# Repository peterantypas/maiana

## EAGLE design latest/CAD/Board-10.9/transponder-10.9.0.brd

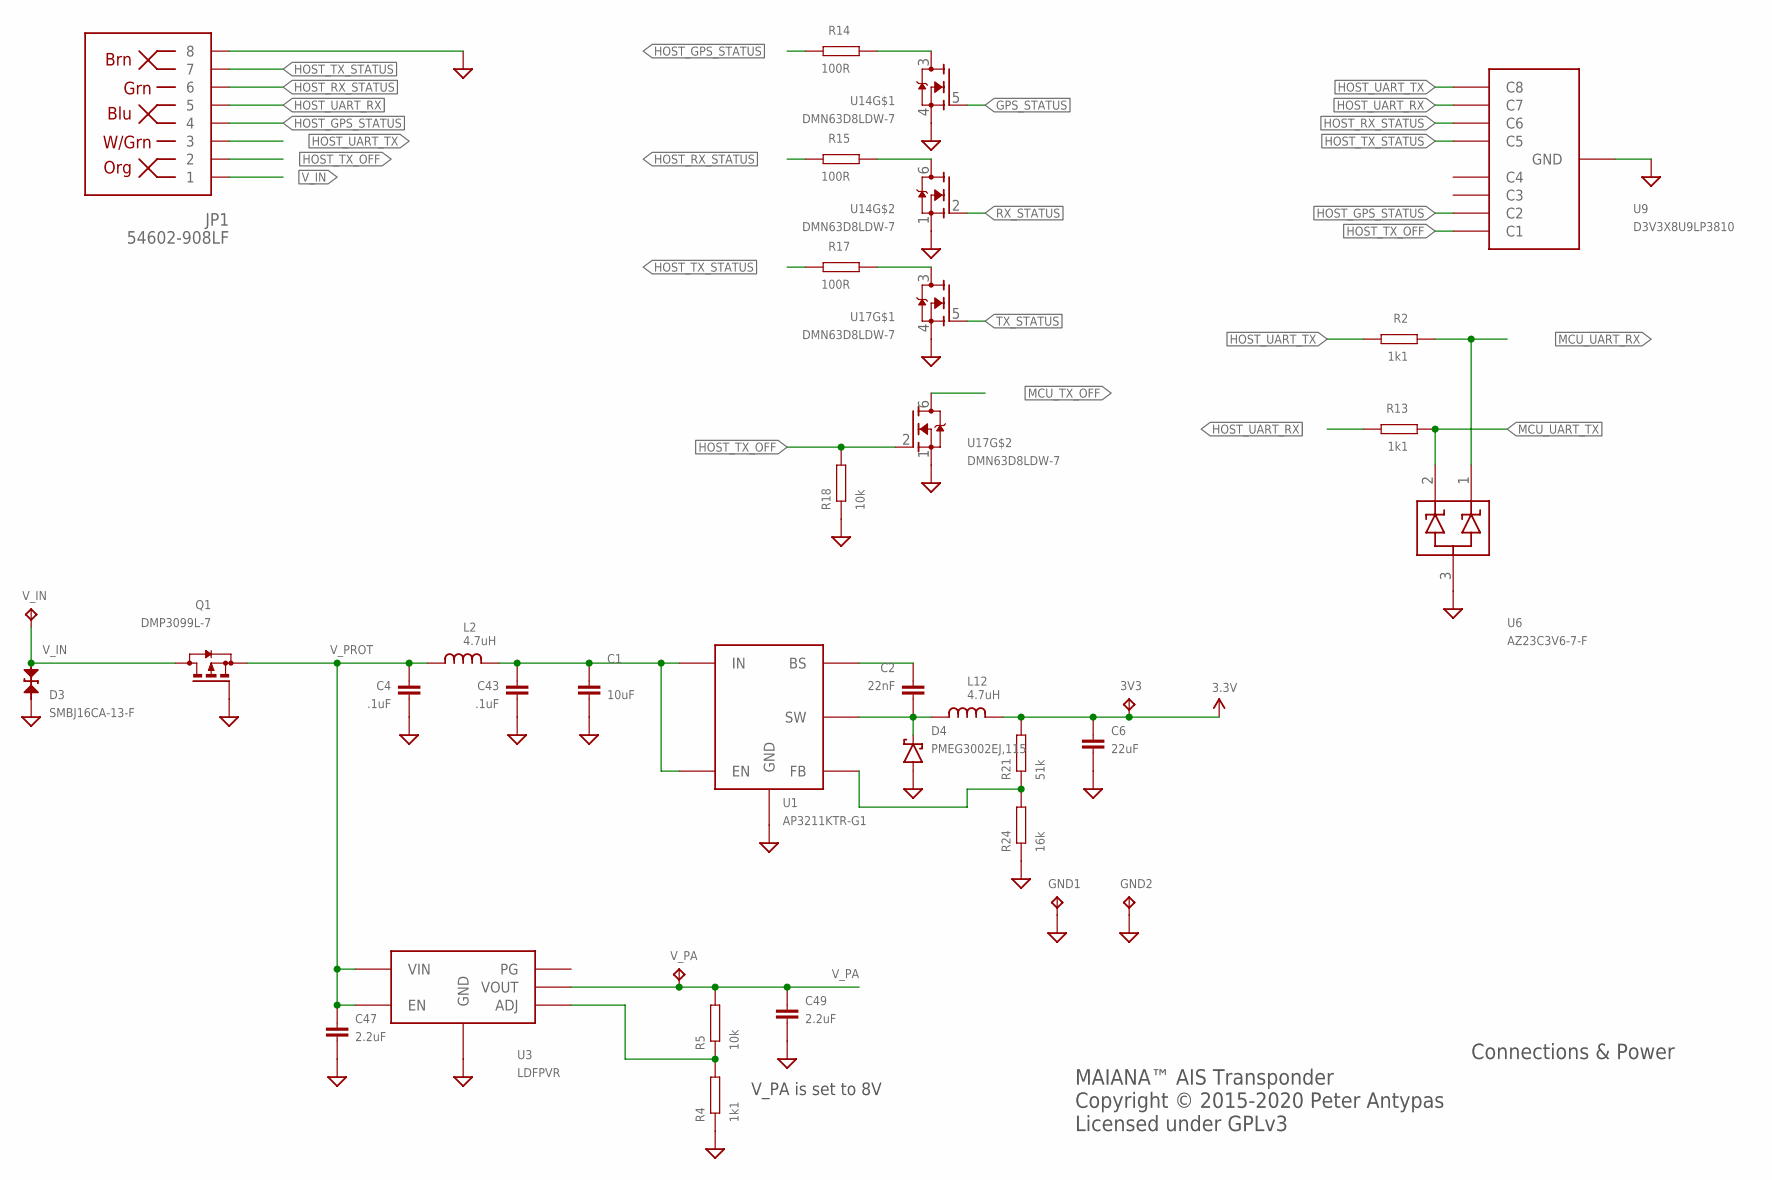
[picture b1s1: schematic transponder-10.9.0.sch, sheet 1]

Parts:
3V3: TPTP12R; TP12R
C1: 10uF; 0805; PARTNO EMK212ABJ106KG-T
C2: 22nF; 0603; PARTNO GRM188R71E223KA01D
C4, C43: .1uF; 0603; PARTNO EMK107B7104KAHT
C6: 22uF; 0805; PARTNO *
C47, C49: 2.2uF; 0603; PARTNO EMK107BJ225KA-T
D3: SMBJ16CA-13-F; SMB-BIDIR; PARTNO SMBJ16CA-13-F
D4: PMEG3002EJ,115; SOD323; PARTNO NSR0240HT1G
GND1, GND2: TPTP12R; TP12R
JP1: 54602-908LF; RJ45-8; PARTNO 54602-908LF‎
L2, L12: 4.7uH; 0805; PARTNO MLZ2012M4R7WT000
Q1: DMP3099L-7; SOT23; PARTNO DMP3099L-7
R2, R4, R13: 1k1; 0603; PARTNO RC0603JR-071K1L
R5, R18: 10k; 0603; PARTNO RC0603JR-0710KL
R14, R15: 100R; 0603; PARTNO RC0603JR-07100RL
R17: 100R; 0603; PARTNO RC0603JR-070RL
R21: 51k; 0603; PARTNO RC0603JR-0751KL
R24: 16k; 0603; PARTNO RC0603FR-1016KL
U1: AP3211KTR-G1; SOT23-6; PARTNO AP3211KTR-G1
U3: LDFPVR; DFN6-2X2; PARTNO LDFPUR
U6: AZ23C3V6-7-F; SOT-23
U9: D3V3X8U9LP3810; U-DFN3810-9(B)
U14, U17: DMN63D8LDW-7; SOT363; PARTNO DMN63D8LDW-7
V_IN: TPTP12R; TP12R
V_PA: TPTP12R; TP12R

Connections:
3.3V: 3V3.TP, C6.P$1 (1), L12.P$2 (2), R21.P$2; also elsewhere on the board
GND: C1.P$2 (2), C4.P$2 (2), C6.P$2 (2), C43.P$2 (2), C47.P$2 (2), C49.P$2 (2), D3.C, D4.A, GND1.TP, GND2.TP, JP1.8, Q1.1 (G), R4.P$1, R18.P$1, R24.P$1, U1.2 (GND), U3.P$4 (GND), U3.P$7 (GND), U6.3, U9.P$3 (GND), U14.1 (S), U14.4 (S), U17.1 (S), U17.4 (S); also elsewhere on the board
GPS_STATUS: U14.5 (G); also elsewhere on the board
HOST_GPS_STATUS: JP1.4, R14.P$2, U9.P$2 (C2)
HOST_RX_STATUS: JP1.6, R15.P$2, U9.P$7 (C6)
HOST_TX_OFF: JP1.2, R18.P$2, U9.P$1 (C1), U17.2 (G)
HOST_TX_STATUS: JP1.7, R17.P$2, U9.P$6 (C5)
HOST_UART_RX: JP1.5, R13.P$2, U9.P$8 (C7)
HOST_UART_TX: JP1.3, R2.P$2, U9.P$9 (C8)
MCU_TX_OFF: U17.6 (D); also elsewhere on the board
MCU_UART_RX: R2.P$1, U6.1; also elsewhere on the board
MCU_UART_TX: R13.P$1, U6.2; also elsewhere on the board
unnamed: C2.P$2 (2), D4.C, L12.P$1 (1), U1.6 (SW)
unnamed: R14.P$1, U14.3 (D)
unnamed: R15.P$1, U14.6 (D)
unnamed: R17.P$1, U17.3 (D)
unnamed: C2.P$1 (1), U1.1 (BS)
unnamed: R21.P$1, R24.P$2, U1.3 (FB)
unnamed: C1.P$1 (1), C43.P$1 (1), L2.P$2 (2), U1.4 (EN), U1.5 (IN)
unnamed: R4.P$2, R5.P$1, U3.P$2 (ADJ)
RX_STATUS: U14.2 (G); also elsewhere on the board
TX_STATUS: U17.5 (G); also elsewhere on the board
V_IN: D3.A, JP1.1, Q1.3 (D), V_IN.TP
V_PA: C49.P$1 (1), R5.P$2, U3.P$1 (VOUT), V_PA.TP; also elsewhere on the board
V_PROT: C4.P$1 (1), C47.P$1 (1), L2.P$1 (1), Q1.2 (S), U3.P$5 (EN), U3.P$6 (VIN)

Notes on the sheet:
Connections & Power
MAIANA™ AIS Transponder Copyright © 2015-2020 Peter Antypas Licensed under GPLv3
V_PA is set to 8V

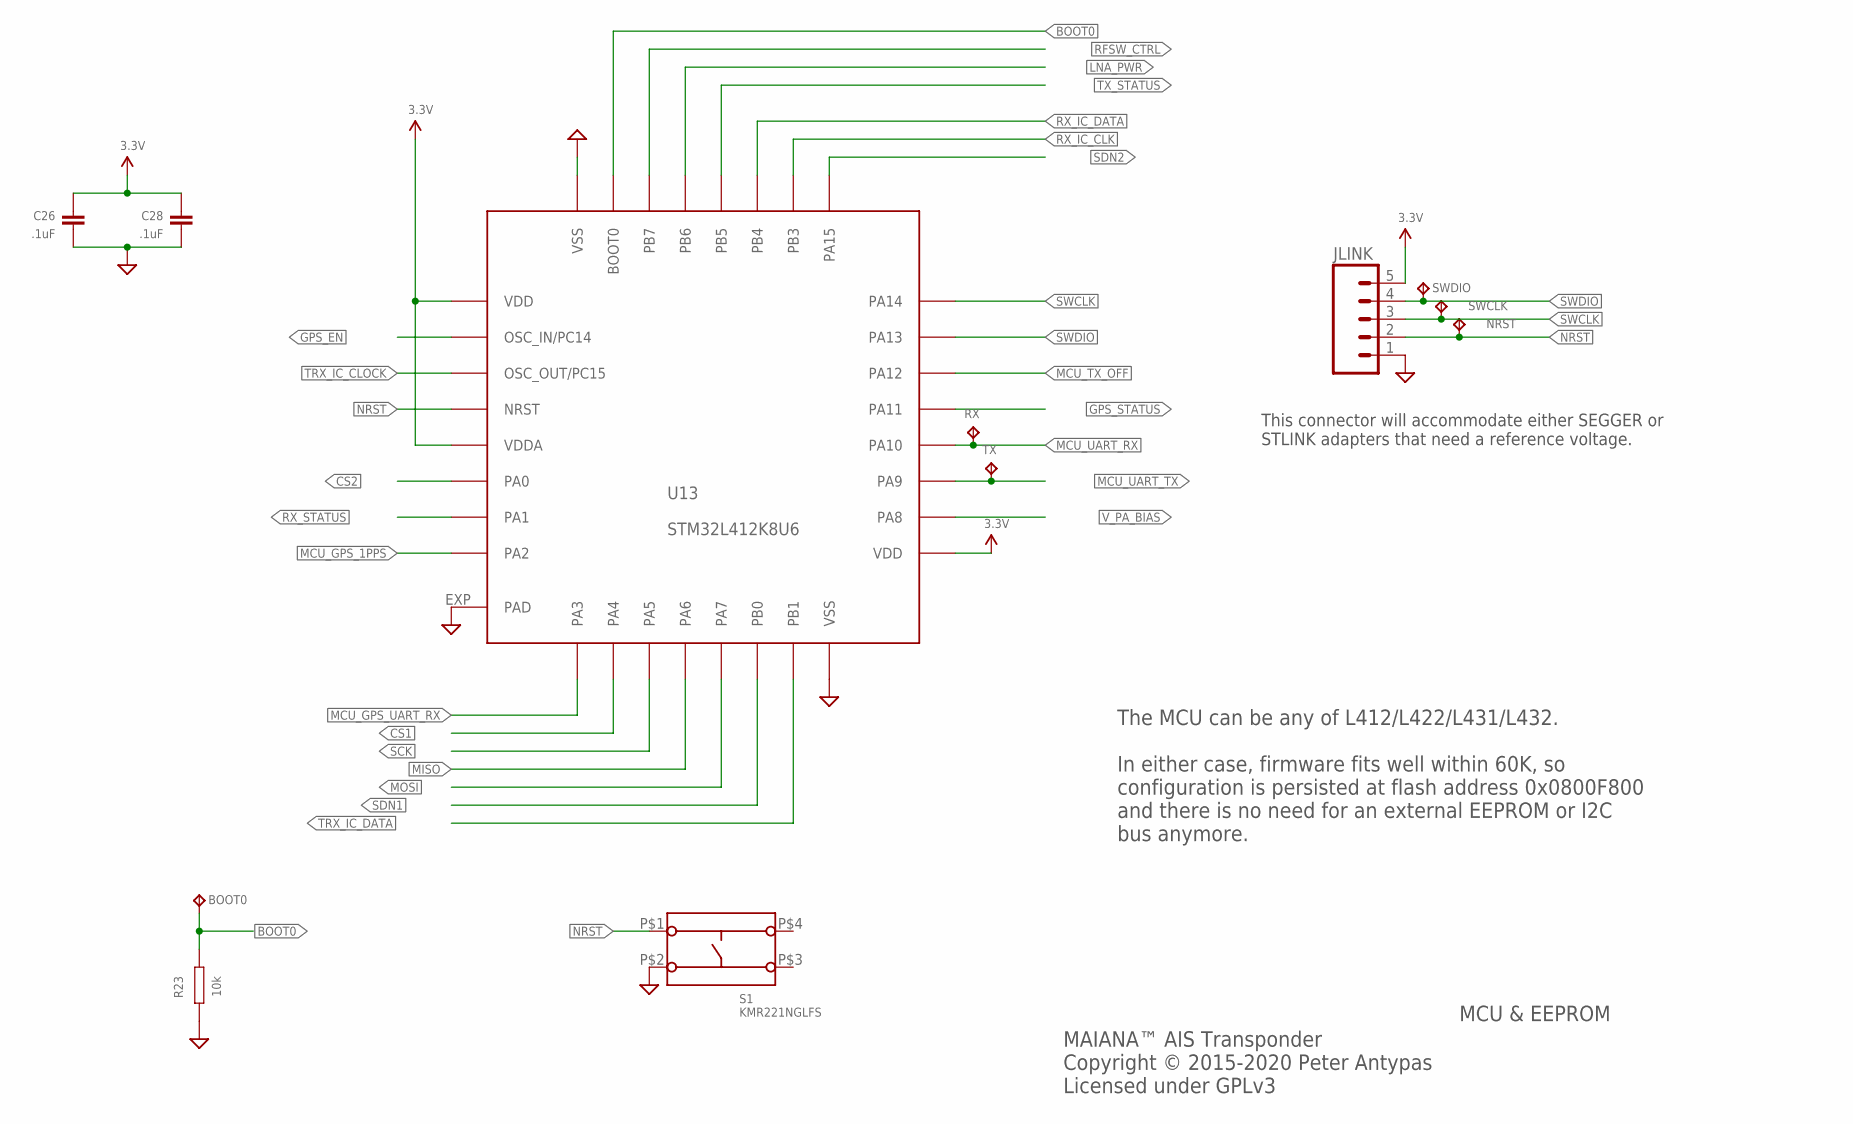
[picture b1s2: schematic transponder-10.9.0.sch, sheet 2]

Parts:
BOOT0: TPTP12R; TP12R
C26, C28: .1uF; 0603; PARTNO EMK107B7104KAHT
JLINK: M05PTH; 1X05
NRST: TPTP12R; TP12R
R23: 10k; 0603; PARTNO RC0603JR-0710KL
RX: TPTP12R; TP12R
S1: KMR221NGLFS
SWCLK: TPTP12R; TP12R
SWDIO: TPTP12R; TP12R
TX: TPTP12R; TP12R
U13: STM32L412K8U6; QFN32; PARTNO STM32L412K8U6

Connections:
3.3V: C26.P$1 (1), C28.P$1 (1), JLINK.5, U13.1 (VDD), U13.5 (VDDA), U13.17 (VDD); also elsewhere on the board
BOOT0: BOOT0.TP, R23.P$1, U13.31 (BOOT0)
CS1: U13.10 (PA4); also elsewhere on the board
CS2: U13.6 (PA0); also elsewhere on the board
GND: C26.P$2 (2), C28.P$2 (2), JLINK.1, R23.P$2, S1.P$2 (S2), U13.16 (VSS), U13.32 (VSS), U13.EXP (PAD); also elsewhere on the board
GPS_EN: U13.2 (OSC_IN/PC14); also elsewhere on the board
GPS_STATUS: U13.21 (PA11); also elsewhere on the board
LNA_PWR: U13.29 (PB6); also elsewhere on the board
MCU_GPS_1PPS: U13.8 (PA2); also elsewhere on the board
MCU_GPS_UART_RX: U13.9 (PA3); also elsewhere on the board
MCU_TX_OFF: U13.22 (PA12); also elsewhere on the board
MCU_UART_RX: RX.TP, U13.20 (PA10); also elsewhere on the board
MCU_UART_TX: TX.TP, U13.19 (PA9); also elsewhere on the board
MISO: U13.12 (PA6); also elsewhere on the board
MOSI: U13.13 (PA7); also elsewhere on the board
NRST: JLINK.2, NRST.TP, S1.P$1 (S1), U13.4 (NRST)
RFSW_CTRL: U13.30 (PB7); also elsewhere on the board
RX_IC_CLK: U13.26 (PB3); also elsewhere on the board
RX_IC_DATA: U13.27 (PB4); also elsewhere on the board
RX_STATUS: U13.7 (PA1); also elsewhere on the board
SCK: U13.11 (PA5); also elsewhere on the board
SDN1: U13.14 (PB0); also elsewhere on the board
SDN2: U13.25 (PA15); also elsewhere on the board
SWCLK: JLINK.3, SWCLK.TP, U13.24 (PA14)
SWDIO: JLINK.4, SWDIO.TP, U13.23 (PA13)
TRX_IC_CLOCK: U13.3 (OSC_OUT/PC15); also elsewhere on the board
TRX_IC_DATA: U13.15 (PB1); also elsewhere on the board
TX_STATUS: U13.28 (PB5); also elsewhere on the board
V_PA_BIAS: U13.18 (PA8); also elsewhere on the board

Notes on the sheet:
MCU & EEPROM
MAIANA™ AIS Transponder Copyright © 2015-2020 Peter Antypas Licensed under GPLv3
The MCU can be any of L412/L422/L431/L432. In either case, firmware fits well within 60K, so configuration is persisted at flash address 0x0800F800 and there is no need for an external EEPROM or I2C bus anymore.
This connector will accommodate either SEGGER or STLINK adapters that need a reference voltage.

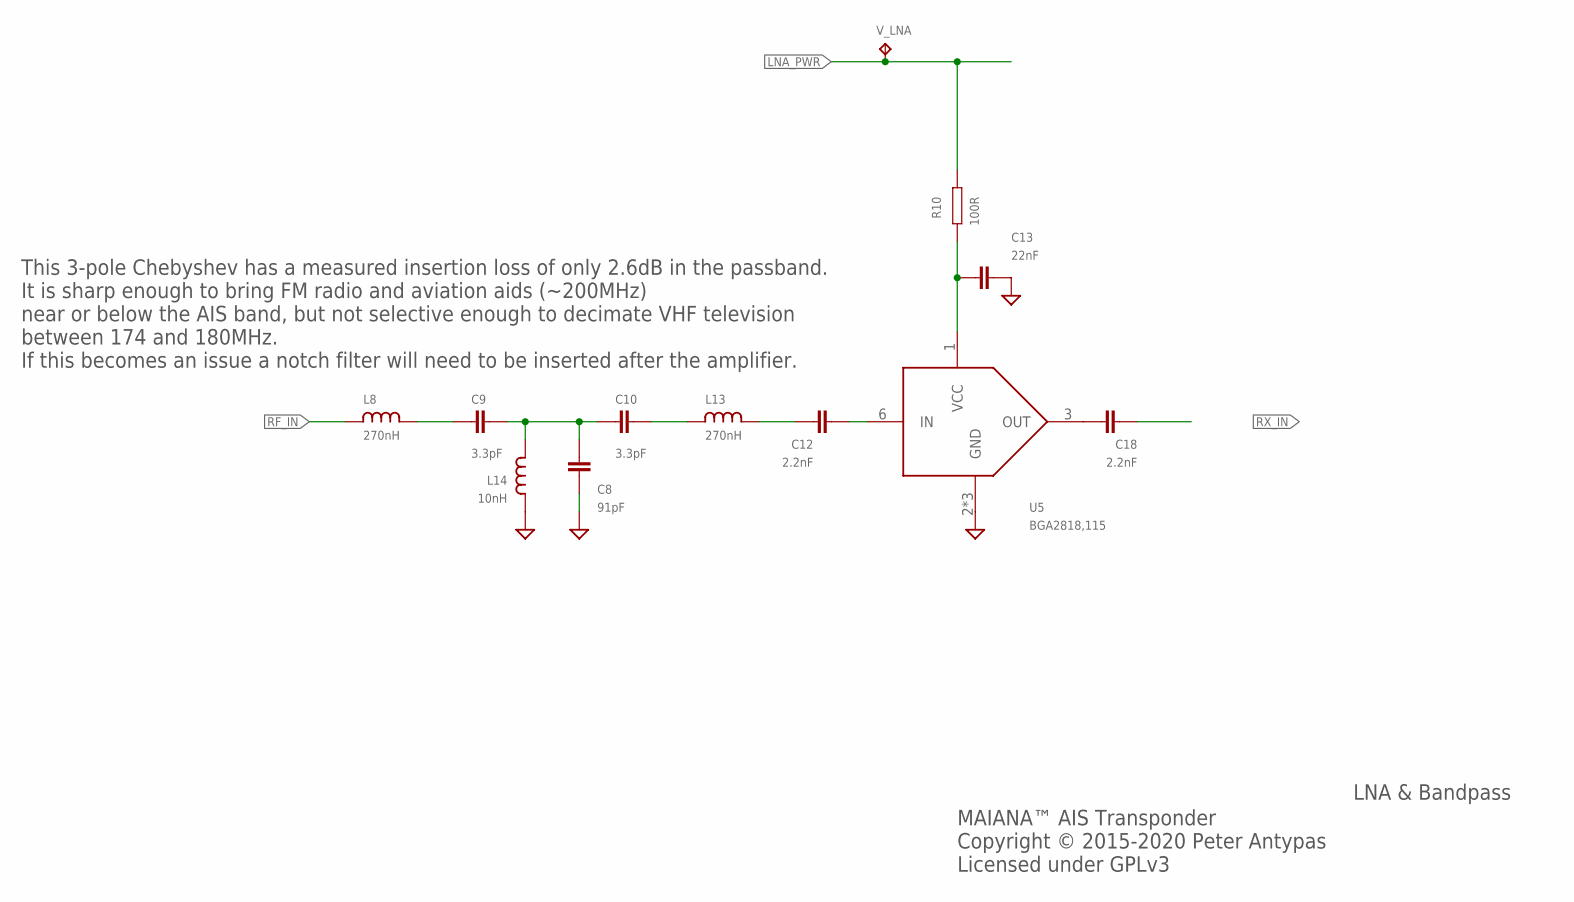
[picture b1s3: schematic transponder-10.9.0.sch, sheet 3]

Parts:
C8: 91pF; 0603; PARTNO GRM1885C2A910JA01D
C9, C10: 3.3pF; 0603; PARTNO GRM1885C1H3R3BA01D
C12, C18: 2.2nF; 0603; PARTNO GRM1885C1H222JA01J
C13: 22nF; 0603; PARTNO GRM188R71E223KA01D
L8, L13: 270nH; 0603; PARTNO LQW18ANR27J00D
L14: 10nH; 0603; PARTNO LQW18AN10NG00D
R10: 100R; 0603; PARTNO RC0603JR-07100RL
U5: BGA2818,115; SOT363; PARTNO BGA2818,115
V_LNA: TPTP12R; TP12R

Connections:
GND: C8.P$2 (2), C13.P$2 (2), L14.P$1 (1), U5.2 (GND), U5.4 (GND), U5.5 (GND); also elsewhere on the board
LNA_PWR: R10.P$1, V_LNA.TP; also elsewhere on the board
unnamed: C12.P$2 (2), U5.6 (IN)
unnamed: C9.P$1 (1), L8.P$2 (2)
unnamed: C8.P$1 (1), C9.P$2 (2), C10.P$1 (1), L14.P$2 (2)
unnamed: C10.P$2 (2), L13.P$1 (1)
unnamed: C12.P$1 (1), L13.P$2 (2)
unnamed: C13.P$1 (1), R10.P$2, U5.1 (VCC)
unnamed: C18.P$1 (1), U5.3 (OUT)
RF_IN: L8.P$1 (1); also elsewhere on the board
RX_IN: C18.P$2 (2); also elsewhere on the board

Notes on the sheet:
LNA & Bandpass
MAIANA™ AIS Transponder Copyright © 2015-2020 Peter Antypas Licensed under GPLv3
This 3-pole Chebyshev has a measured insertion loss of only 2.6dB in the passband. It is sharp enough to bring FM radio and aviation aids (~200MHz) near or below the AIS band, but not selective enough to decimate VHF television between 174 and 180MHz. If this becomes an issue a notch filter will ne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

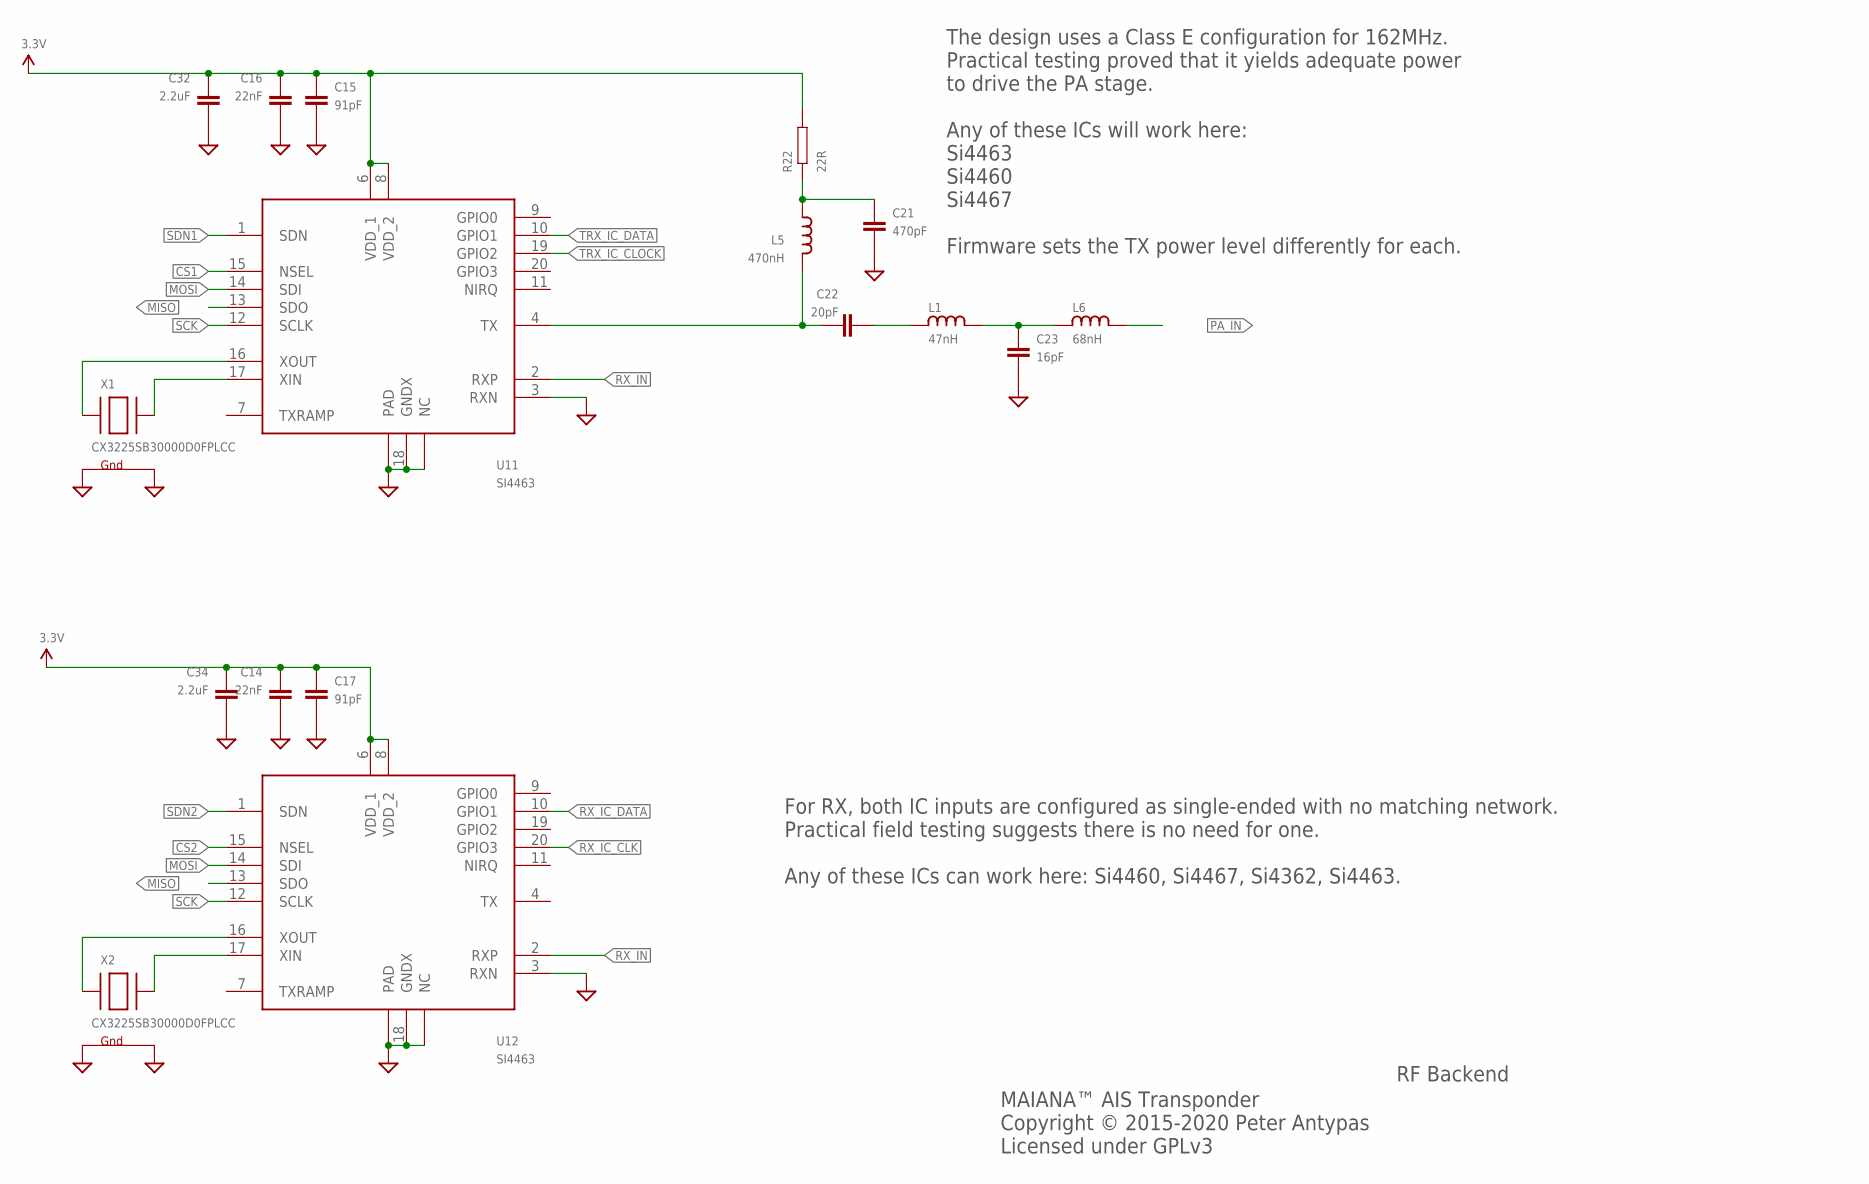
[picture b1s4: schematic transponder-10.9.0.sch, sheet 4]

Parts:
C14, C16: 22nF; 0603; PARTNO GRM188R71E223KA01D
C15, C17: 91pF; 0603; PARTNO GRM1885C2A910JA01D
C21: 470pF; 0603; PARTNO GRM1885C1H471JA01D
C22: 20pF; 0603; PARTNO GRM1885C1H200JA01D
C23: 16pF; 0603; PARTNO GCM1885C2A160JA16D
C32, C34: 2.2uF; 0603; PARTNO EMK107BJ225KA-T
L1: 47nH; 0603; PARTNO LQW18AN47NG00D
L5: 470nH; 0603; PARTNO HK1608R47J-T
L6: 68nH; 0603
R22: 22R; 0603; PARTNO RC0603JR-0722RL
U11, U12: SI4463; PARTNO SI4463-C2A-GMR
X1, X2: CX3225SB30000D0FPLCC; NX3225; PARTNO CX3225SB30000D0FPLCC

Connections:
3.3V: C14.P$1 (1), C15.P$1 (1), C16.P$1 (1), C17.P$1 (1), C32.P$1 (1), C34.P$1 (1), R22.P$2, U11.6 (VDD_1), U11.8 (VDD_2), U12.6 (VDD_1), U12.8 (VDD_2); also elsewhere on the board
CS1: U11.15 (NSEL); also elsewhere on the board
CS2: U12.15 (NSEL); also elsewhere on the board
GND: C14.P$2 (2), C15.P$2 (2), C16.P$2 (2), C17.P$2 (2), C21.P$2 (2), C23.P$2 (2), C32.P$2 (2), C34.P$2 (2), U11.3 (RXN), U11.5 (NC), U11.18 (GNDX), U11.EXP (PAD), U12.3 (RXN), U12.5 (NC), U12.18 (GNDX), U12.EXP (PAD), X1.2 (G2), X1.4 (G1), X2.2 (G2), X2.4 (G1); also elsewhere on the board
MISO: U11.13 (SDO), U12.13 (SDO); also elsewhere on the board
MOSI: U11.14 (SDI), U12.14 (SDI); also elsewhere on the board
unnamed: C23.P$1 (1), L1.P$2 (2), L6.P$1 (1)
unnamed: U12.16 (XOUT), X2.1 (X1)
unnamed: U12.17 (XIN), X2.3 (X2)
unnamed: U11.16 (XOUT), X1.1 (X1)
unnamed: U11.17 (XIN), X1.3 (X2)
unnamed: C22.P$1 (1), L5.P$2 (2), U11.4 (TX)
unnamed: C21.P$1 (1), L5.P$1 (1), R22.P$1
unnamed: C22.P$2 (2), L1.P$1 (1)
PA_IN: L6.P$2 (2); also elsewhere on the board
RX_IC_CLK: U12.20 (GPIO3); also elsewhere on the board
RX_IC_DATA: U12.10 (GPIO1); also elsewhere on the board
RX_IN: U11.2 (RXP), U12.2 (RXP); also elsewhere on the board
SCK: U11.12 (SCLK), U12.12 (SCLK); also elsewhere on the board
SDN1: U11.1 (SDN); also elsewhere on the board
SDN2: U12.1 (SDN); also elsewhere on the board
TRX_IC_CLOCK: U11.19 (GPIO2); also elsewhere on the board
TRX_IC_DATA: U11.10 (GPIO1); also elsewhere on the board

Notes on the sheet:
RF Backend
MAIANA™ AIS Transponder Copyright © 2015-2020 Peter Antypas Licensed under GPLv3
The design uses a Class E configuration for 162MHz. Practical testing proved that it yields adequate power to drive the PA stage. Any of these ICs will work here: Si4463 Si4460 Si4467 Firmware sets the TX power level differently for each.
For RX, both IC inputs are configured as single-ended with no matching network. Practical field testing suggests there is no need for one. Any of these ICs can work here: Si4460, Si4467, Si4362, Si4463.

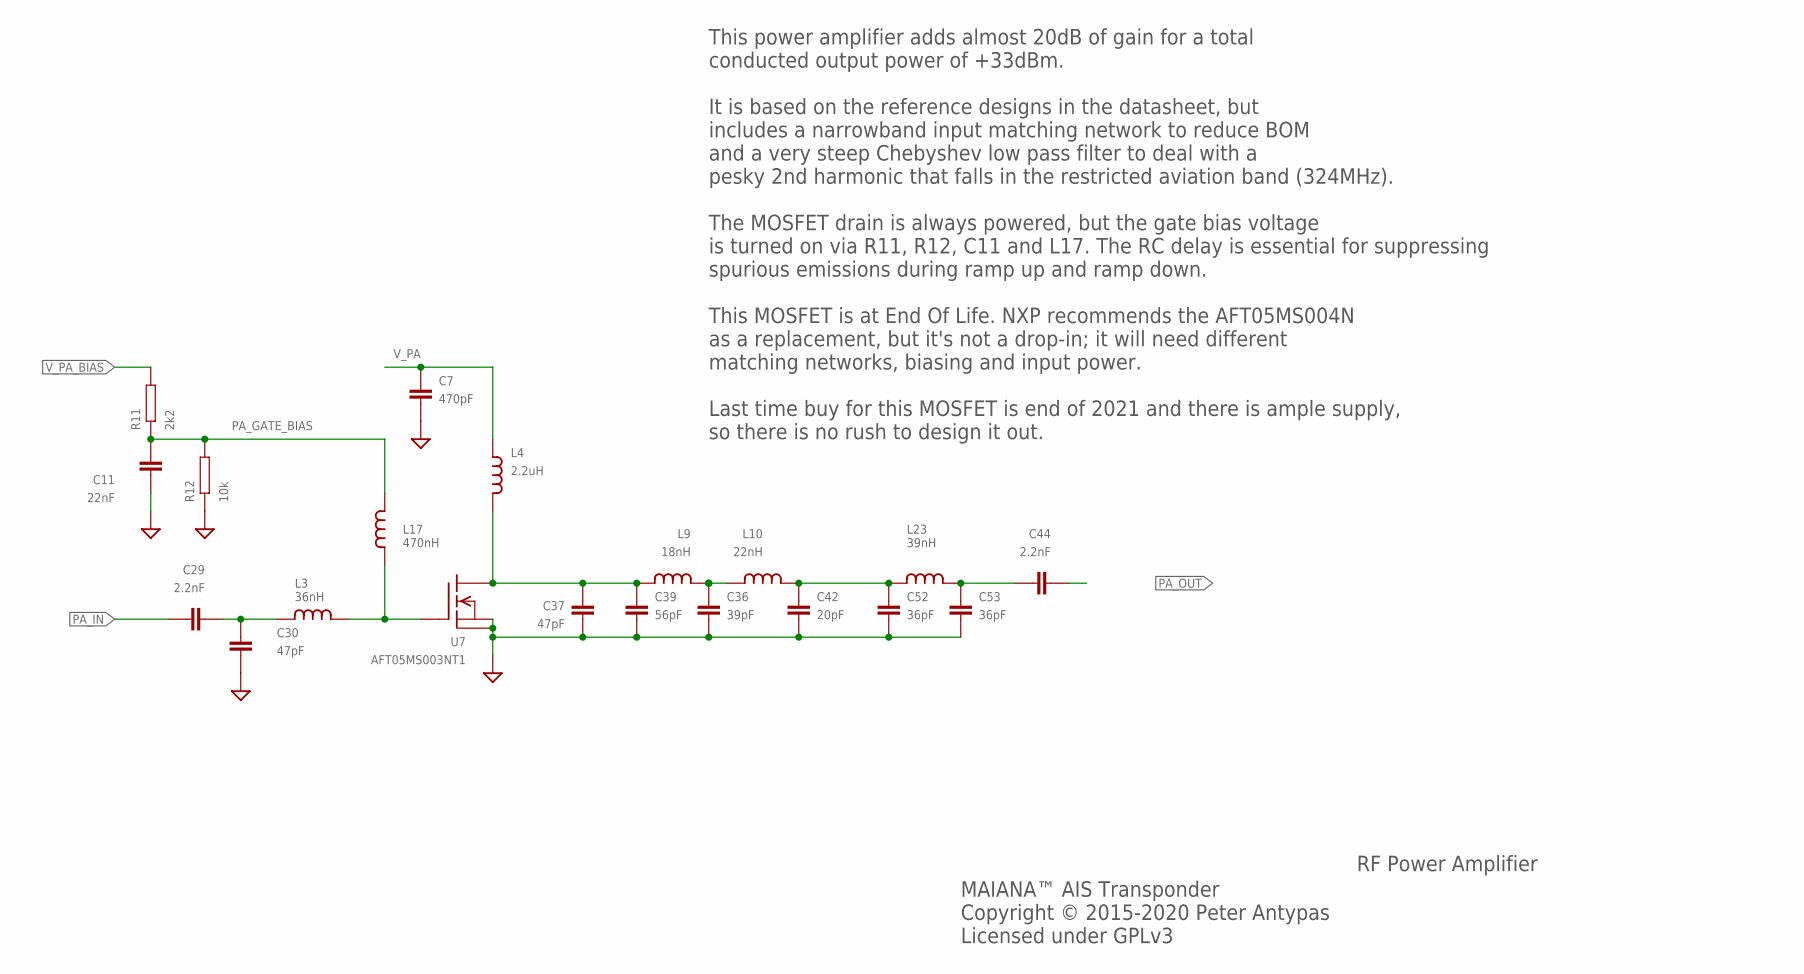
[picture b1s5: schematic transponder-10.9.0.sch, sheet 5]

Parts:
C7: 470pF; 0603; PARTNO GRM1885C1H471JA01D
C11: 22nF; 0603; PARTNO GRM188R71E223KA01D
C29, C44: 2.2nF; 0603; PARTNO GRM1885C1H222JA01J
C30, C37: 47pF; 0603; PARTNO GRM1885C1H470JA01J
C36: 39pF; 0603; PARTNO GRM1885C1H390JA01D
C39: 56pF; 0603; PARTNO GRM1885C1H560JA01D
C42: 20pF; 0603; PARTNO GRM1885C1H200JA01D
C52, C53: 36pF; 0603; PARTNO 06035A360JAT2A
L3: 36nH; 0603; PARTNO LQW18AN36NG00D
L4: 2.2uH; 0805; PARTNO BRC2012T2R2MD
L9: 18nH; 0603; PARTNO LQW18AN18NG00D
L10: 22nH; 0603; PARTNO LQW18AN22NJ00D
L17: 470nH; 0603; PARTNO HK1608R47J-T
L23: 39nH; 0603; PARTNO LQW18AN39NG00D
R11: 2k2; 0603; PARTNO RC0603FR-072K2L
R12: 10k; 0603; PARTNO RC0603JR-0710KL
U7: AFT05MS003NT1; SOT-89; PARTNO AFT05MS003NT1

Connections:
GND: C7.P$2 (2), C11.P$2 (2), C30.P$2 (2), C36.P$2 (2), C37.P$2 (2), C39.P$2 (2), C42.P$2 (2), C52.P$2 (2), C53.P$2 (2), R12.P$1, U7.2 (S), U7.2@1 (PAD); also elsewhere on the board
unnamed: C37.P$1 (1), C39.P$1 (1), L4.P$2 (2), L9.P$1 (1), U7.3 (D)
unnamed: L3.P$2 (2), L17.P$1 (1), U7.1 (G)
unnamed: C36.P$1 (1), L9.P$2 (2), L10.P$1 (1)
unnamed: C29.P$2 (2), C30.P$1 (1), L3.P$1 (1)
unnamed: C42.P$1 (1), C52.P$1 (1), L10.P$2 (2), L23.P$1 (1)
unnamed: C44.P$1 (1), C53.P$1 (1), L23.P$2 (2)
PA_GATE_BIAS: C11.P$1 (1), L17.P$2 (2), R11.P$1, R12.P$2
PA_IN: C29.P$1 (1); also elsewhere on the board
PA_OUT: C44.P$2 (2); also elsewhere on the board
V_PA: C7.P$1 (1), L4.P$1 (1); also elsewhere on the board
V_PA_BIAS: R11.P$2; also elsewhere on the board

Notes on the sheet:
RF Power Amplifier
MAIANA™ AIS Transponder Copyright © 2015-2020 Peter Antypas Licensed under GPLv3
This power amplifier adds almost 20dB of gain for a total conducted output power of +33dBm. It is based on the reference designs in the datasheet, but includes a narrowband input matching network to reduce BOM and a very steep Chebyshev low pass filter to deal with a pesky 2nd harmonic that falls i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

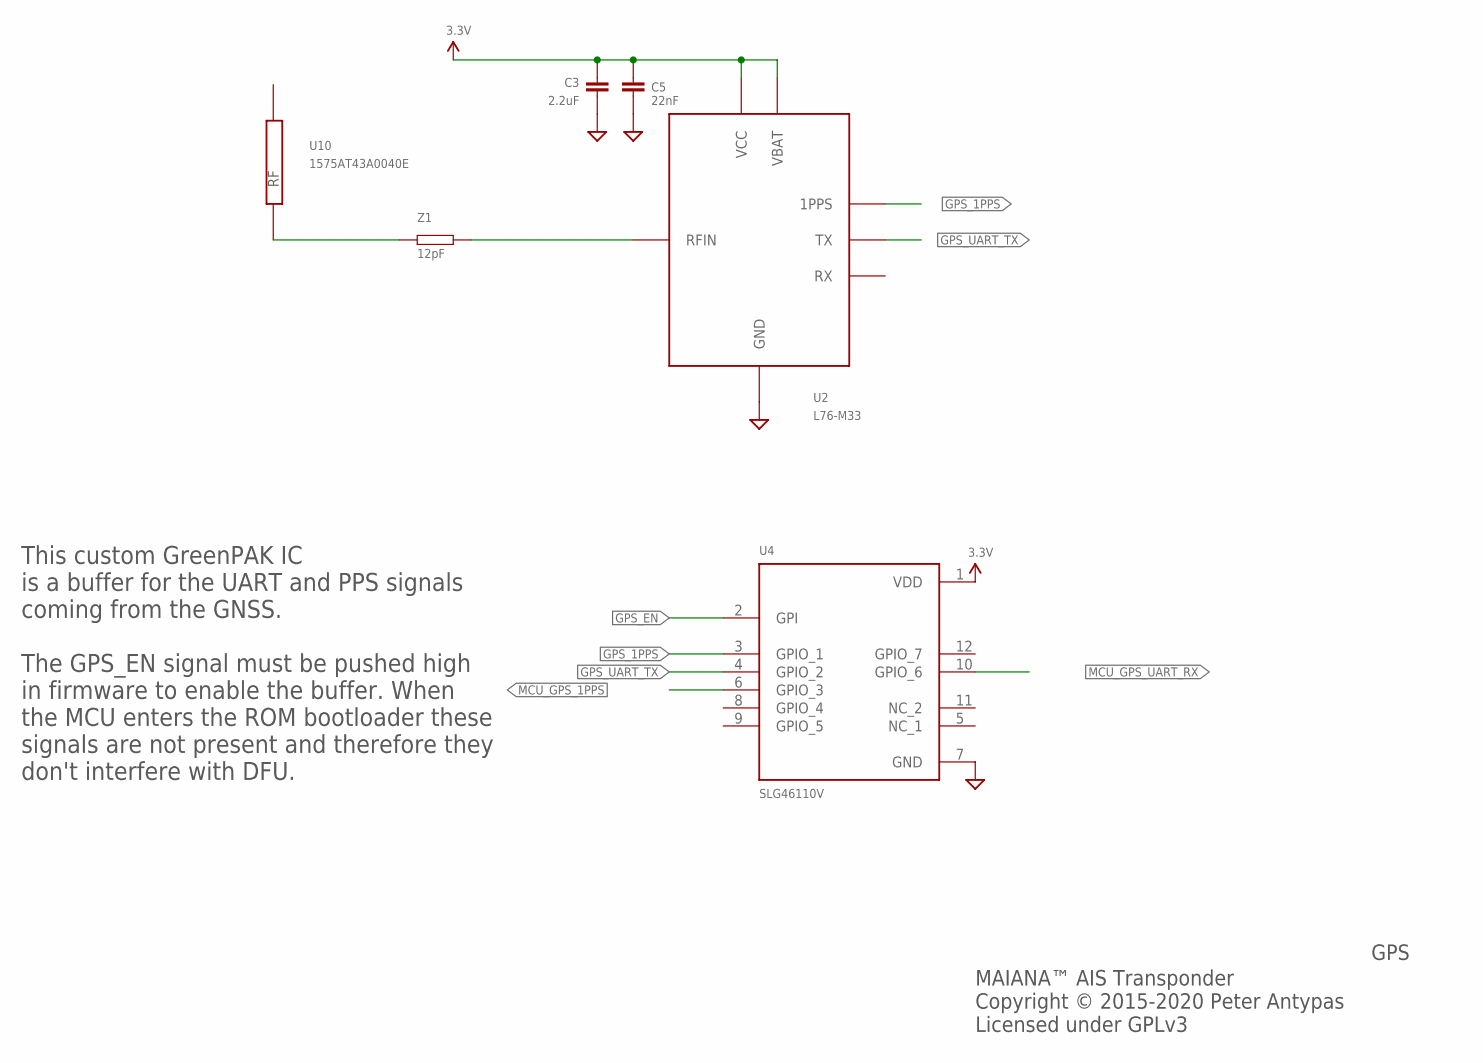
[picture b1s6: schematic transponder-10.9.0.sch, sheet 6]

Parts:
C3: 2.2uF; 0603; PARTNO EMK107BJ225KA-T
C5: 22nF; 0603; PARTNO GRM188R71E223KA01D
U2: L76-M33; GPS_MODULE; PARTNO L70B-M39
U4: SLG46110V; IC_SLG46110V
U10: 1575AT43A0040E; PARTNO 1575AT43A0040E
Z1: 12pF; 0603; PARTNO ‎GRM1885C1H120GA01D‎

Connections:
3.3V: C3.P$1 (1), C5.P$1 (1), U2.P$6 (VBAT), U2.P$8 (VCC), U4.1 (VDD); also elsewhere on the board
GND: C3.P$2 (2), C5.P$2 (2), U2.P$1 (GND), U2.P$10 (GND), U2.P$12 (GND), U4.7 (GND); also elsewhere on the board
GPS_1PPS: U2.P$4 (1PPS), U4.3 (GPIO_1)
GPS_EN: U4.2 (GPI); also elsewhere on the board
GPS_UART_TX: U2.P$2 (TX), U4.4 (GPIO_2)
MCU_GPS_1PPS: U4.6 (GPIO_3); also elsewhere on the board
MCU_GPS_UART_RX: U4.10 (GPIO_6); also elsewhere on the board
unnamed: U10.P$1 (RF), Z1.P$1
unnamed: U2.P$11 (RFIN), Z1.P$2

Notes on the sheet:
GPS
MAIANA™ AIS Transponder Copyright © 2015-2020 Peter Antypas Licensed under GPLv3
This custom GreenPAK IC is a buffer for the UART and PPS signals coming from the GNSS. The GPS_EN signal must be pushed high in firmware to enable the buffer. When the MCU enters the ROM bootloader these signals are not present and therefore they don't interfere with DFU.

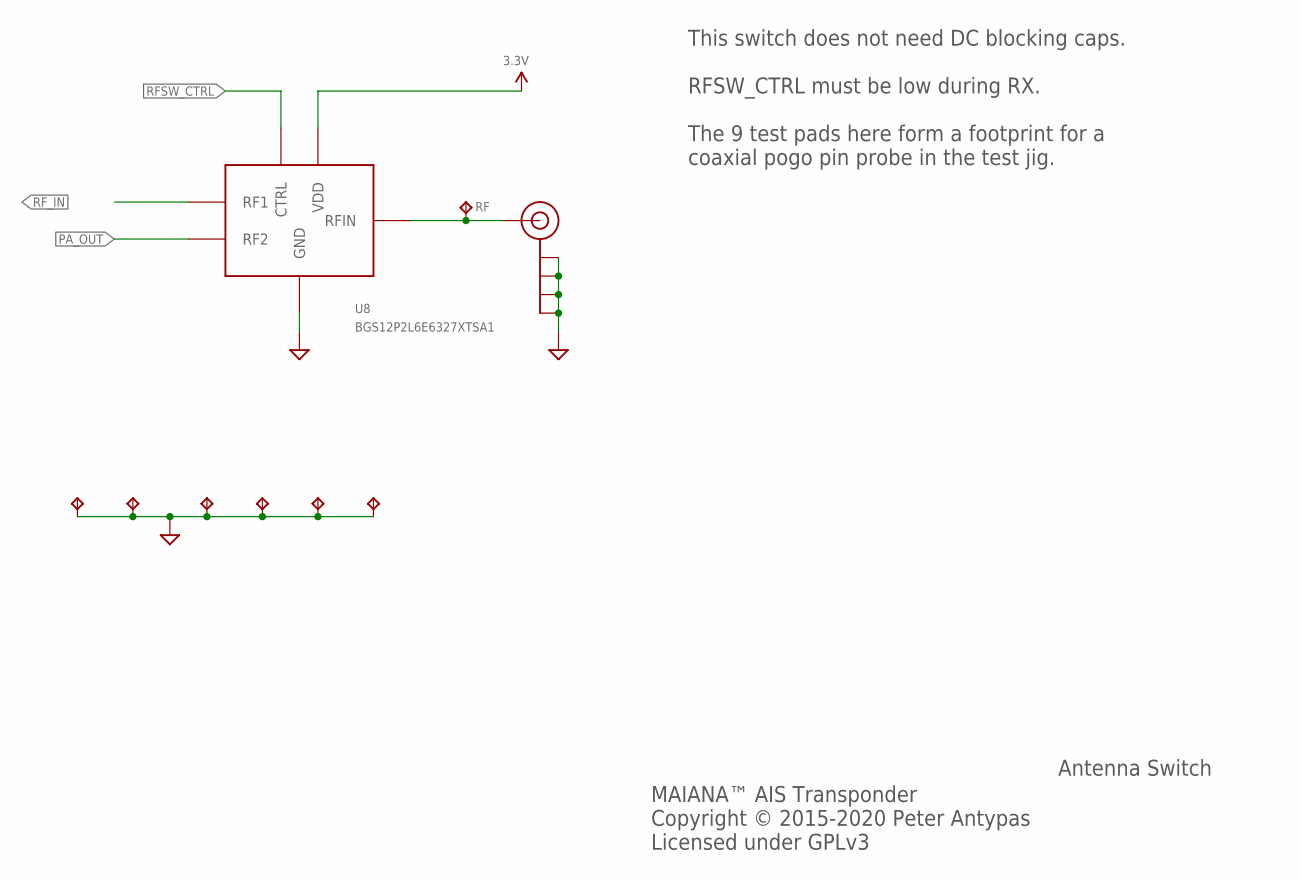
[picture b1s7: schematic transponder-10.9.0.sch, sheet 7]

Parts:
J$1: SMA_EDGE; SMA-EDGE
RF: TPTP10R; TP10R
SWDIO1, SWDIO2, SWDIO3, SWDIO4, SWDIO5, SWDIO6: TPTP12R; TP12R
U8: BGS12P2L6E6327XTSA1; PSON50P145X100X50-6N; PARTNO ‎BGS12P2L6E6327XTSA1‎

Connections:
3.3V: U8.4 (VDD); also elsewhere on the board
GND: J$1.GND@0 (GND), J$1.GND@1 (GND), J$1.GND@2 (GND), J$1.GND@3 (GND), SWDIO1.TP, SWDIO2.TP, SWDIO3.TP, SWDIO4.TP, SWDIO5.TP, SWDIO6.TP, U8.2 (GND); also elsewhere on the board
unnamed: J$1.SIG (SIGNAL), RF.TP, U8.5 (RFIN)
PA_OUT: U8.1 (RF2); also elsewhere on the board
RFSW_CTRL: U8.6 (CTRL); also elsewhere on the board
RF_IN: U8.3 (RF1); also elsewhere on the board

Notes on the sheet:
Antenna Switch
MAIANA™ AIS Transponder Copyright © 2015-2020 Peter Antypas Licensed under GPLv3
This switch does not need DC blocking caps. RFSW_CTRL must be low during RX. The 9 test pads here form a footprint for a coaxial pogo pin probe in the test jig.

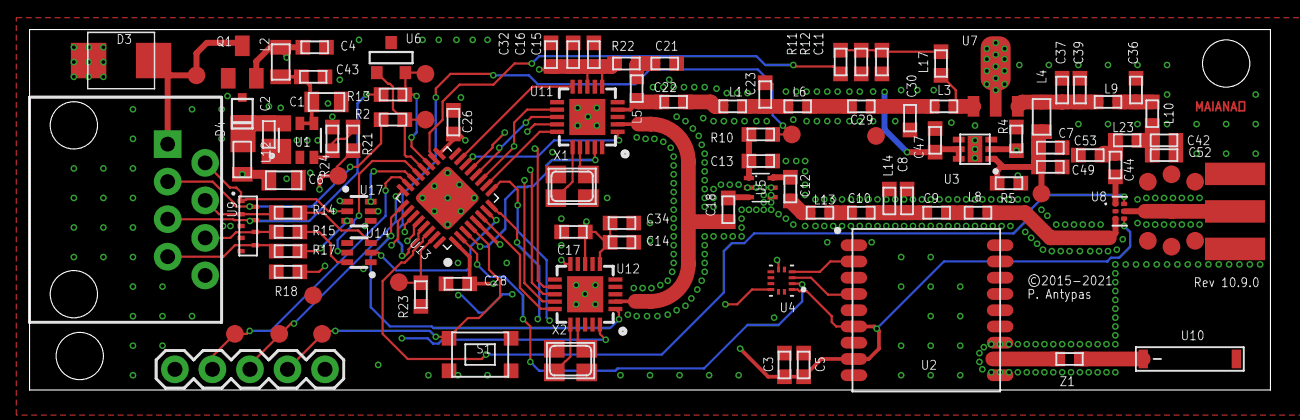
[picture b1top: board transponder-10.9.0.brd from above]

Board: 4 copper layers, 84.0 x 24.4 mm, 110 parts (0 on the bottom side), 77 nets.

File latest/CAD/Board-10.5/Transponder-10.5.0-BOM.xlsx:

Qty | PartNo | Description | Value | Package | Reference Designators
2 | 1N4148WTQ-7 | Standard SMD silicon diode | 1N4148WTQ-7 | SOD523 | D5, D6
1 | 1575AT43A0040E | SMD Ceramic GNSS Antenna | 1575AT43A0040E | 1575AT43A0040E | U10
2 | 06035A360JAT2A | Standard SMD capacitor | 36pF | 0603 | C52, C53
1 | 54602-908LF‎ | RJ45 Jack | RJ45 | RJ45-8 | JP1
1 | AFT05MS003NT1 | RF MOSFET | AFT05MS003NT1 | SOT-89 | U7
1 | AP3211KTR-G1 | Buck converter | AP3211KTR-G1 | SOT23-6 | U1
1 | BAT41ZFILM | Diode | 250MA/100V | SOD-323 | D4
1 | BGA2818,115 | MMIC Wideband Amplifier | BGA2818,115 | SOT363 | U5
1 | BRC2012T2R2MD | Standard SMD inductor | 2.2uH | 0805 | L4
2 | BZT52C3V6T-7 | Zener Diode | BZT52C3V6T-7 | SOD523 | D1, D2
2 | CX3225SB30000D0FPLCC | Classic 4-pin 3.2 x 2.5mm crystal | CX3225SB30000D0FPLCC | NX3225 | X1, X2
1 | D3V3X8U9LP3810 | 8 CHANNEL LOW CAPACITANCE TVS DIODE ARRAY | D3V3X8U9LP3810 | U-DFN3810-9(B) | U9
3 | DMN63D8LDW-7 | Dual N-Channel MOSFET | DMN63D8LDW-7 | SOT363 | U4, U14, U17
1 | DMP3099L-7 | P-CHANNEL MOS FET | DMP3099L-7 | SOT23 | Q1
4 | EMK107B7104KAHT | Standard SMD capacitor | .1uF | 0603 | C4, C26, C28, C43
5 | EMK107BJ225KA-T | Standard SMD capacitor | 2.2uF | 0603 | C3, C32, C34, C47, C49
1 | EMK212ABJ106KG-T | Standard SMD capacitor | 10uF | 0805 | C1
1 | GCM1885C2A160JA16D | Standard SMD capacitor | 16pF | 0603 | C23
1 | GRM21BR61A226ME51L | Standard SMD capacitor | 22uF | 0805 | C6
6 | GRM188R71E223KA01D | Standard SMD capacitor | 22nF | 0603 | C2, C5, C11, C13, C14, C16
2 | GRM1885C1H3R3BA01D | Standard SMD capacitor | 3.3pF | 0603 | C9, C10
2 | GRM1885C1H200JA01D | Standard SMD capacitor | 20pF | 0603 | C22, C42
4 | GRM1885C1H222JA01J | Standard SMD capacitor | 2.2nF | 0603 | C12, C18, C29, C44
1 | GRM1885C1H390JA01D | Standard SMD capacitor | 39pF | 0603 | C36
2 | GRM1885C1H470JA01J | Standard SMD capacitor | 47pF | 0603 | C30, C37
2 | GRM1885C1H471JA01D | Standard SMD capacitor | 470pF | 0603 | C7, C21
1 | GRM1885C1H560JA01D | Standard SMD capacitor | 56pF | 0603 | C39
2 | GRM1885C2A240JA01D | Standard SMD capacitor | 24pF | 0603 | C24, C25
3 | GRM1885C2A910JA01D | Standard SMD capacitor | 91pF | 0603 | C8, C15, C17
2 | HK1608R47J-T | Standard SMD inductor | 470nH | 0603 | L5, L17
1 | L76-M33 | GNSS Module | L76-M33 | GPS_MODULE | U2
1 | LDFPVR | 1A Adjustable LDO | LDFPVR | DFN6-2X2 | U3
1 | LQW18AN10NG00D | Standard SMD inductor | 10nH | 0603 | L14
1 | LQW18AN18NG00D | Standard SMD inductor | 18nH | 0603 | L9
1 | LQW18AN22NJ00D | Standard SMD inductor | 22nH | 0603 | L10
1 | LQW18AN36NG00D | Standard SMD inductor | 36nH | 0603 | L3
1 | LQW18AN39NG00D | Standard SMD inductor | 39nH | 0603 | L23
1 | LQW18AN47NG00D | Standard SMD inductor | 47nH | 0603 | L1
1 | LQW18AN56NG00D | Standard SMD inductor | 56nH | 0603 | L11
1 | LQW18ANR10G00D | Standard SMD inductor | 100nH | 0603 | L7
1 | LQW18ANR13J00D | Standard SMD inductor | 130nH | 0603 | L6
2 | LQW18ANR27J00D | Standard SMD inductor | 270nH | 0603 | L8, L13
2 | MLZ2012M4R7WT000 | Standard SMD inductor | 4.7uH | 0805 | L2, L12
1 | RC0603FR-072K4L | Standard SMD resistor | 2k4 | 0603 | R11
1 | RC0603FR-1016KL | Standard SMD resistor | 16k | 0603 | R24
1 | RC0603JR-070RL | Standard SMD resistor | 0R | 0603 | R17
3 | RC0603JR-071K1L | Standard SMD resistor | 1k1 | 0603 | R2, R4, R13
8 | RC0603JR-0710KL | Standard SMD resistor | 10k | 0603 | R3, R5, R6, R7, R12, R16, R18, R23
1 | RC0603JR-0722RL | Standard SMD resistor | 22R | 0603 | R22
1 | RC0603JR-0751KL | Standard SMD resistor | 51k | 0603 | R21
3 | RC0603JR-07100RL | Standard SMD resistor | 100R | 0603 | R10, R14, R15
2 | SI4463-C2A-GMR |  | SI4463 | SI4463 | U11, U12
1 | SKY13330-397LF | SP2T RF Switch | SKY13330-397LF | QFN12 | U15
1 | SMBJ16CA-13-F | Bidirectional TVS diode | SMBJ16CA-13-F | SMB-BIDIR | D3
1 | STM32L412K8U6 |  | STM32L412K8U6 | QFN32 | U13
1 | ‎GRM1885C1H120GA01D‎ | Standard SMD capacitor | 12pF | 0603 | Z1

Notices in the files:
latest/CAD/Board-10.9/transponder-10.9.0.brd:
©2015-2021
latest/CAD/Board-4.3/transponder-4.3.brd:
(c)2017
latest/CAD/Board-5.0/transponder-5.0.brd:
(c)2016-2020
parts and their libraries:
SparkFun-Connectors: Licensing: Creative Commons ShareAlike 4.0 International - https://creativecommons.org/licenses/by-sa/4.0
